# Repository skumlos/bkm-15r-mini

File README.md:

BKM-15R-mini, an alternative to the Sony BKM-15R controller for your BVM-A series monitor.

A small PCB that connects to an ESP32 Devkit V1 and an ENC28J60 module.

The ESP32 module should be the 30-pin "Devkit V1" which seems pretty common. Note that an 36-pin version also exists, the
"original" Doit ESP32 Devkit V1", this version needs some "hacking" to work.

The ENC28J60 module exists in many versions. The one designed in here, is the 12-pin 5V version, sometimes referred to as "the large" version.
It should run on 5V and have 12 pins (apparently a very close version with 10 pins running straight on 3.3V also exists).

The ESP32 should be loaded with the code from here: https://github.com/skumlos/bkm-15rduino

The "Disable WiFi" switch, disables wifi... I like hard switches for stuff like this.
It's handy if you just want the physical keys (you could comment out all WiFi stuff from the code also of course...).

Press the FORCE_SETUP switch while pressing the RESET switch, to make the software go into configuration mode for WiFi setup and such.

Use a crossed ethernet cable or a switch between this and the BVM-A.

The ESP32 footprint and library symbol is originally by David Kleymann (https://github.com/davidkleymann/doit-esp32-devkit-kicad).
I modified it to fit the seemingly more common 30 pin version of the ESP32 Devkit V1.

3D printable case on thingiverse.com

(2022) Martin Hejnfelt (martin@hejnfelt.com)
www.immerhax.com

This work is free. You can redistribute it and/or modify it under the
terms of the Do What The Fuck You Want To Public License, Version 2,
as published by Sam Hocevar. See the LICENSE file for more details.

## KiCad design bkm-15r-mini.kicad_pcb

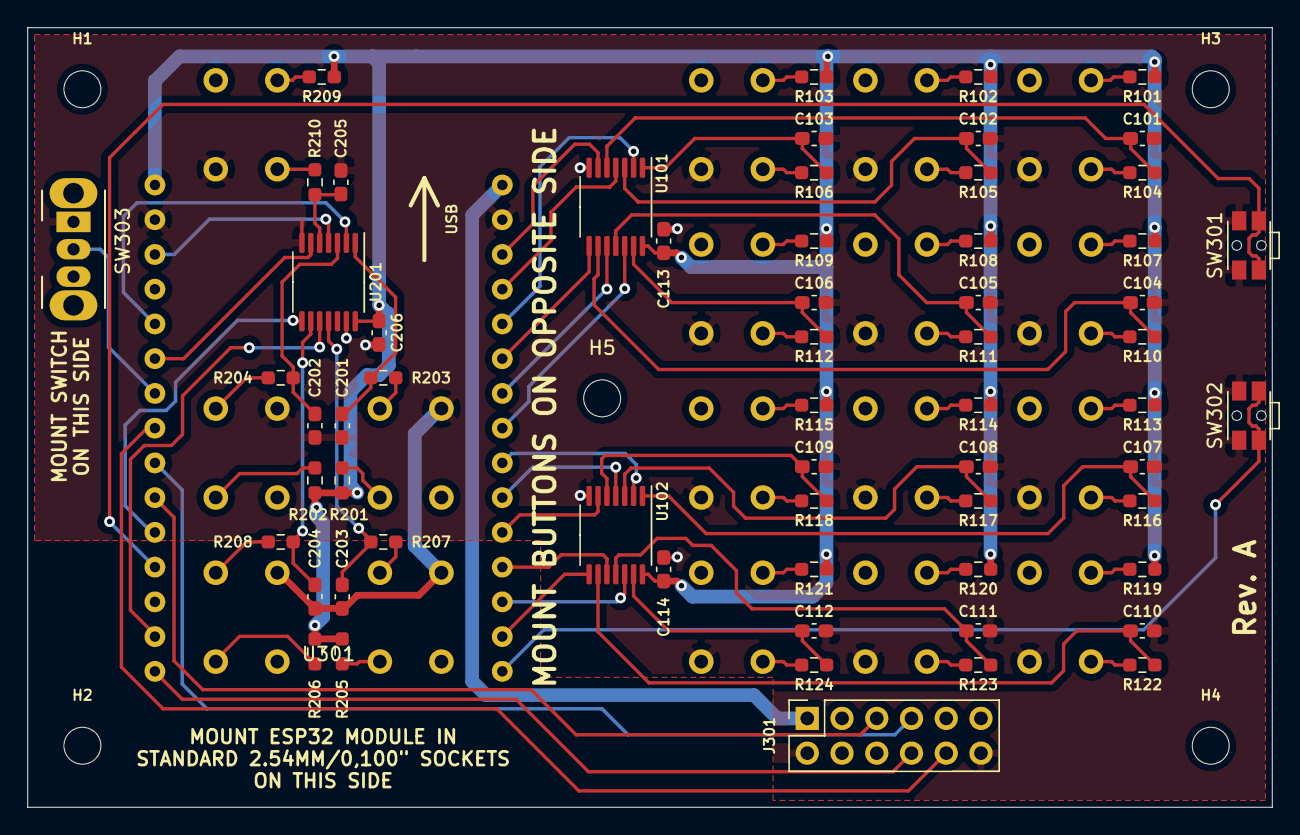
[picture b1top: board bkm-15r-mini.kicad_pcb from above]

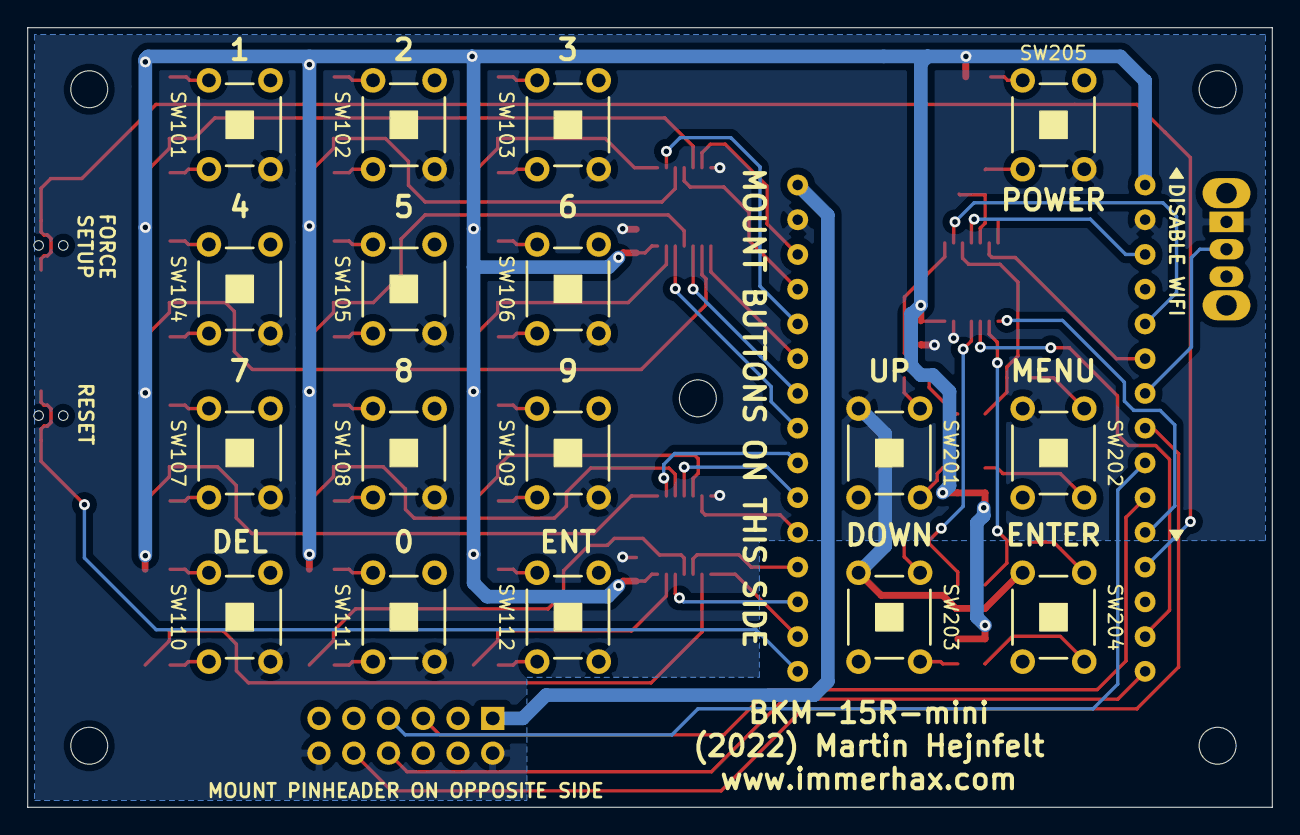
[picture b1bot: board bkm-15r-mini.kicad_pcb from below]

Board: 2 copper layers, 91.0 x 57.0 mm, 84 parts (17 on the bottom side), 78 nets.

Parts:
C101, C102, C103, C104, C105, C106, C107, C108, C109, C110, C111, C112, C201, C202, C203, C204, C205: 10nF; C_0603_1608Metric_Pad1.08x0.95mm_HandSolder
C113, C114, C206: 100nF; C_0603_1608Metric_Pad1.08x0.95mm_HandSolder
H1, H2, H3, H4, H5: MountingHole; MountingHole_2.7mm_M2.5
J301: ENC28J60; PinSocket_2x06_P2.54mm_Vertical
R101, R102, R103, R104, R105, R106, R107, R108, R109, R110, R111, R112, R113, R114, R115, R116, R117, R118, R119, R120, R121, R122, R123, R124, R201, R202, R203, R204, R205, R206, R207, R208, R209, R210: 10K; R_0603_1608Metric_Pad0.98x0.95mm_HandSolder
SW101, SW102, SW103, SW104, SW105, SW106, SW107, SW108, SW109, SW110, SW111, SW112, SW201, SW202, SW203, SW204, SW205: TL-1240-NO_LED
SW301: SW_ForceSetup; SW_SPST_EVQP7C
SW302: SW_Reset; SW_SPST_EVQP7C
SW303: OS102011MA1QN1C; SW_CuK_OS102011MA1QN1_SPDT_Angled
U101, U102, U201: 74HC14; TSSOP-14_4.4x5mm_P0.65mm
U301: DOIT-ESP32-DEVKIT-V1_30PIN; ESP32-DOIT-DEVKIT_30PIN

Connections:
+3V3: C113.2, C114.2, C206.2, R101.1, R102.1, R103.1, R107.1, R108.1, R109.1, R113.1, R114.1, R115.1, R119.1, R120.1, R121.1, R201.1, R202.1, R205.1, R206.1, R209.1, U101.14, U102.14, U201.14, U301.22
+5V: J301.1, U301.15
CS: J301.10, U301.29
DISABLE_WIFI: SW303.2, U301.28
FORCE_SETUP: SW301.2, U301.33
GND: C101.2, C102.2, C103.2, C104.2, C105.2, C106.2, C107.2, C108.2, C109.2, C110.2, C111.2, C112.2, C113.1, C114.1, C201.2, C202.2, C203.2, C204.2, C205.2, C206.1, J301.2, J301.12, SW101.3, SW102.3, SW103.3, SW104.3, SW105.3, SW106.3, SW107.3, SW108.3, SW109.3, SW110.3, SW111.3, SW112.3, SW201.3, SW202.3, SW203.3, SW204.3, SW205.3, SW301.1, SW302.1, SW303.1, U101.7, U102.7, U201.7, U201.13, U301.14, U301.23
INPUT_KEY0: U102.10, U301.4
INPUT_KEY1: U101.6, U301.13
INPUT_KEY2: U101.4, U301.12
INPUT_KEY3: U101.2, U301.11
INPUT_KEY4: U101.8, U301.10
INPUT_KEY5: U101.10, U301.9
INPUT_KEY6: U101.12, U301.8
INPUT_KEY7: U102.2, U301.7
INPUT_KEY8: U102.4, U301.6
INPUT_KEY9: U102.6, U301.5
INPUT_KEY_DEL: U102.8, U301.2
INPUT_KEY_ENT: U102.12, U301.3
KEY_POWER: U201.6, U301.27
NAV_KEY_DOWN: U201.10, U301.35
NAV_KEY_ENTER: U201.8, U301.32
NAV_KEY_MENU: U201.4, U301.24
NAV_KEY_UP: U201.2, U301.26
unnamed: C101.1, R104.1, U101.5
unnamed: C102.1, R105.1, U101.3
unnamed: C103.1, R106.1, U101.1
unnamed: C104.1, R110.1, U101.9
unnamed: C105.1, R111.1, U101.11
unnamed: C106.1, R112.1, U101.13
unnamed: C107.1, R116.1, U102.1
unnamed: C108.1, R117.1, U102.3
unnamed: C109.1, R118.1, U102.5
unnamed: C110.1, R122.1, U102.9
unnamed: C111.1, R123.1, U102.11
unnamed: C112.1, R124.1, U102.13
unnamed: C201.1, R203.1, U201.1
unnamed: C202.1, R204.1, U201.3
unnamed: C203.1, R207.1, U201.11
unnamed: C204.1, R208.1, U201.9
unnamed: C205.1, R210.1, U201.5
unnamed: R101.2, SW101.2
unnamed: R102.2, SW102.2
unnamed: R103.2, SW103.2
unnamed: R104.2, SW101.1
unnamed: R105.2, SW102.1
unnamed: R106.2, SW103.1
unnamed: R107.2, SW104.2
unnamed: R108.2, SW105.2
unnamed: R109.2, SW106.2
unnamed: R110.2, SW104.1
unnamed: R111.2, SW105.1
unnamed: R112.2, SW106.1
unnamed: R113.2, SW107.2
unnamed: R114.2, SW108.2
unnamed: R115.2, SW109.2
unnamed: R116.2, SW107.1
unnamed: R117.2, SW108.1
unnamed: R118.2, SW109.1
unnamed: R119.2, SW110.2
unnamed: R120.2, SW111.2
unnamed: R121.2, SW112.2
unnamed: R122.2, SW110.1
unnamed: R123.2, SW111.1
unnamed: R124.2, SW112.1
unnamed: R201.2, SW201.2
unnamed: R202.2, SW202.2
unnamed: R203.2, SW201.1
unnamed: R204.2, SW202.1
unnamed: R205.2, SW203.2
unnamed: R206.2, SW204.2
unnamed: R207.2, SW203.1
unnamed: R208.2, SW204.1
unnamed: R209.2, SW205.2
unnamed: R210.2, SW205.1
RESET: SW302.2, U301.1
SCK: J301.7, U301.30
SO: J301.5, U301.31
ST: J301.8, U301.36

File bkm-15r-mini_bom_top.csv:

"Comment","Designator","Footprint","LCSC Part #"
"74HC14","U101 U102 U201","TSSOP-14","C6066"
"10K","R101 R104 R107 R110 R113 R116 R102 R105 R103 R106 R108 R111 R109 R112 R114 R117 R115 R118 R121 R124 R120 R123 R119 R122 R201 R203 R202 R204 R205 R207 R206 R208 R209 R210","0603","C98220"
"10nF","C101 C104 C107 C102 C103 C105 C106 C108 C109 C112 C111 C110 C201 C202 C203 C204 C205","0603","C115056"
"100nF","C113 C114 C206","0603","C14663"
"ENC28J60","J301","",""
"SW_ForceSetup","SW301","SMD","C388883"
"SW_Reset","SW302","SMD","C388883"
"OS102011MA1QN1C","SW303","",""
"DOIT-ESP32-DEVKIT-V1_30PIN","U301","",""

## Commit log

2022-04-07 Add Rev. A plot
2022-04-14 Update readme for modules
2022-04-21 Add JLCPCB assembly stuff, update plots
2022-04-21 Forgot to save :D
2022-06-30 Add license
2022-07-07 Added top plate by RetroUpgrades
